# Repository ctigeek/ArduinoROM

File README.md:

# ArduinoROM

Open files using [KiCAD](https://kicad.org)

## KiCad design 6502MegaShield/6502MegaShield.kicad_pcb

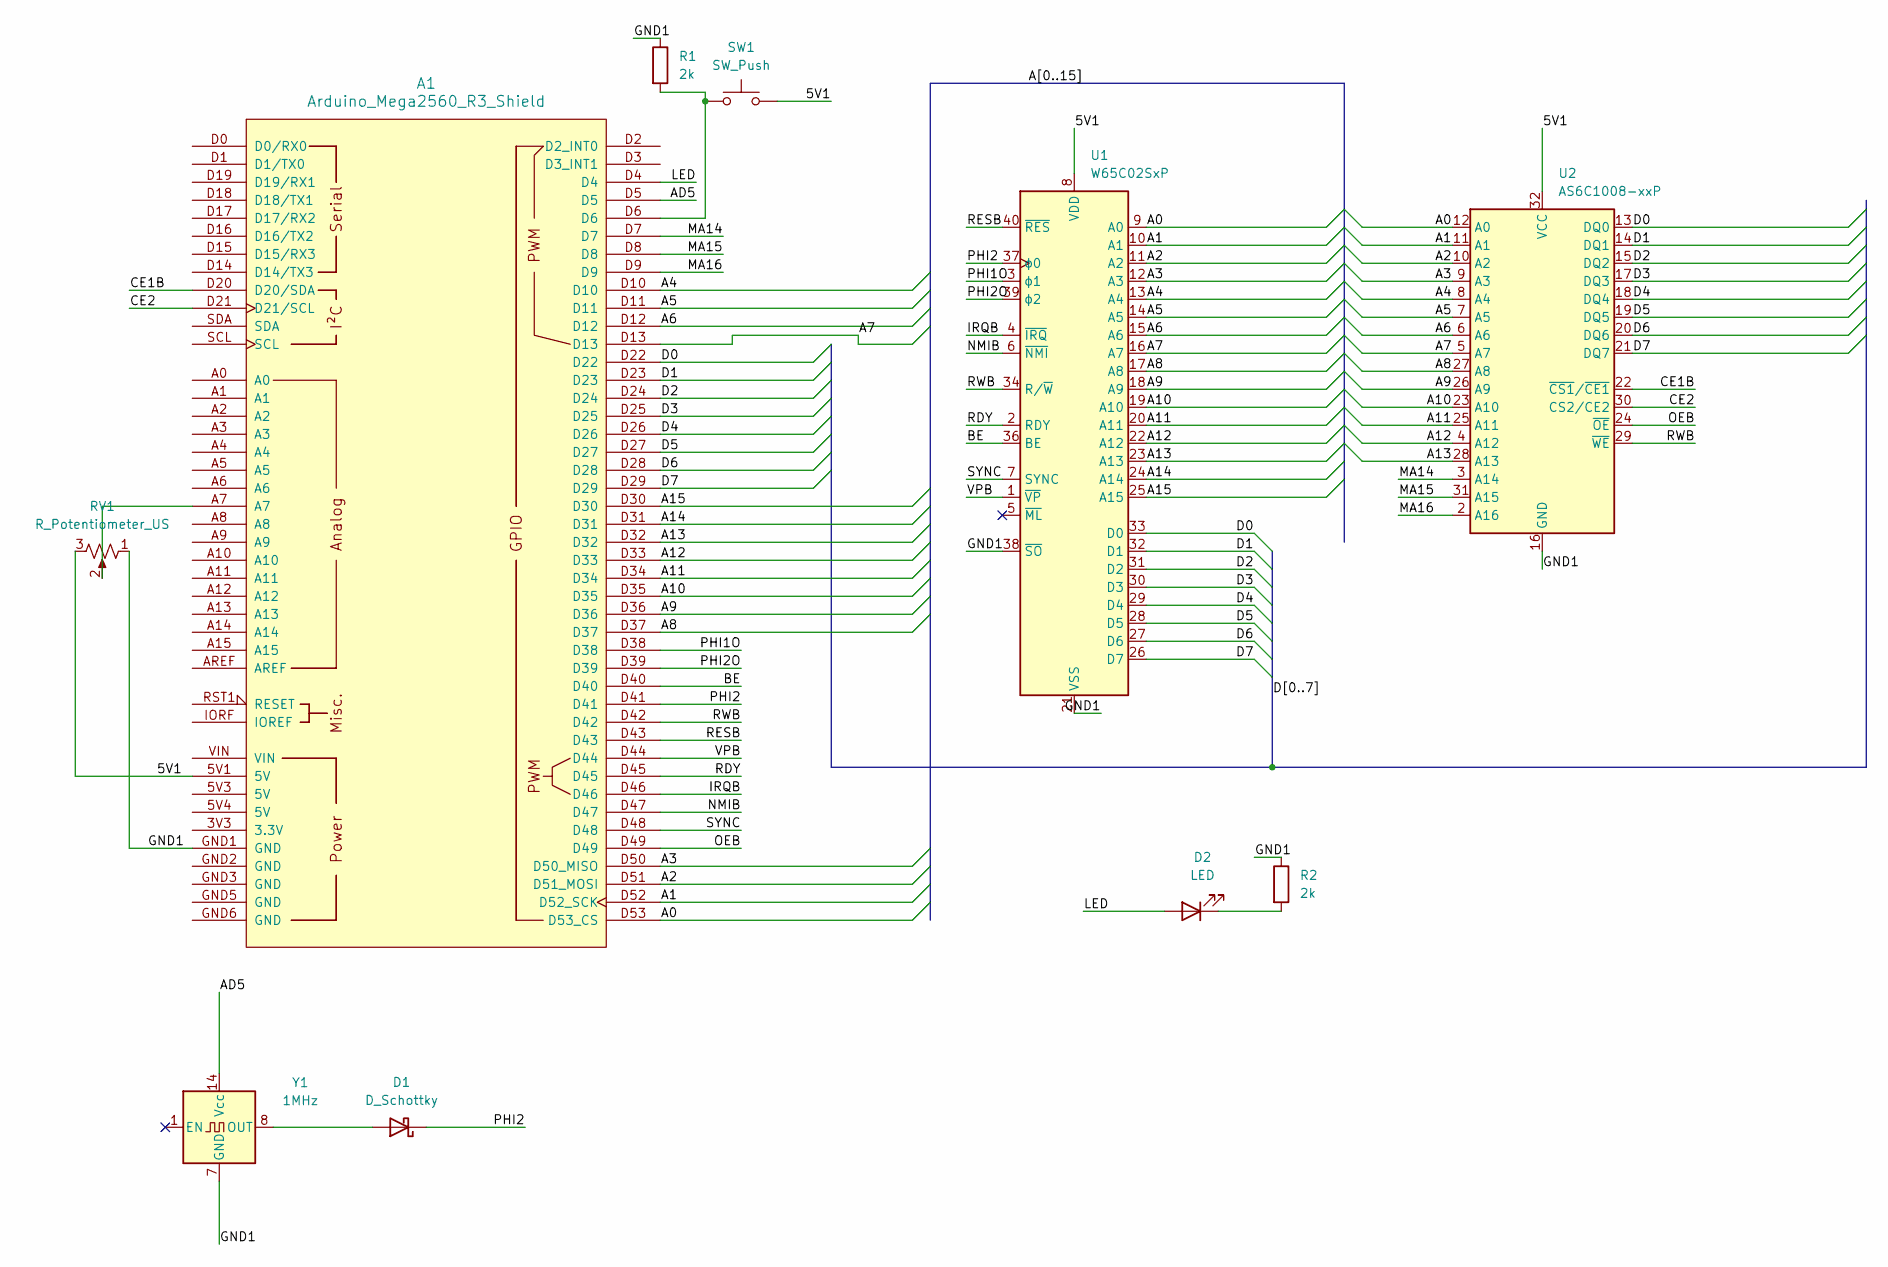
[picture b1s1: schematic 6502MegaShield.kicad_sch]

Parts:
A1: Arduino_Mega2560_R3_Shield
D1: D_Schottky; D_T-1_P5.08mm_Horizontal
D2: LED; LED_D3.0mm
R1, R2: 2k; R_Axial_DIN0204_L3.6mm_D1.6mm_P5.08mm_Horizontal
RV1: R_Potentiometer_US; Potentiometer_Bourns_3386P_Vertical
SW1: SW_Push; SW_PUSH_1P1T_6x3.5mm_H4.3_APEM_MJTP1243
U1: W65C02SxP; DIP-40_W15.24mm
U2: AS6C1008-xxP; DIP-32_W15.24mm
Y1: 1MHz; Oscillator_DIP-14

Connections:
/5V1: A1.5V1 (5V), RV1.3, SW1.2, U1.8 (VDD), U2.32 (VCC)
/A0: A1.D53 (D53_CS), U1.9 (A0), U2.12 (A0)
/A1: A1.D52 (D52_SCK), U1.10 (A1), U2.11 (A1)
/A2: A1.D51 (D51_MOSI), U1.11 (A2), U2.10 (A2)
/A3: A1.D50 (D50_MISO), U1.12 (A3), U2.9 (A3)
/A4: A1.D10, U1.13 (A4), U2.8 (A4)
/A5: A1.D11, U1.14 (A5), U2.7 (A5)
/A6: A1.D12, U1.15 (A6), U2.6 (A6)
/A7: A1.D13, U1.16 (A7), U2.5 (A7)
/A8: A1.D37, U1.17 (A8), U2.27 (A8)
/A9: A1.D36, U1.18 (A9), U2.26 (A9)
/A10: A1.D35, U1.19 (A10), U2.23 (A10)
/A11: A1.D34, U1.20 (A11), U2.25 (A11)
/A12: A1.D33, U1.22 (A12), U2.4 (A12)
/A13: A1.D32, U1.23 (A13), U2.28 (A13)
/A14: A1.D31, U1.24 (A14)
/A15: A1.D30, U1.25 (A15)
/AD5: A1.D5, Y1.14 (Vcc)
/BE: A1.D40, U1.36 (BE)
/CE1B: A1.D20 (D20/SDA), U2.22 (~CS1/~CE1)
/CE2: A1.D21 (D21/SCL), U2.30 (CS2/CE2)
/D0: A1.D22, U1.33 (D0), U2.13 (DQ0)
/D1: A1.D23, U1.32 (D1), U2.14 (DQ1)
/D2: A1.D24, U1.31 (D2), U2.15 (DQ2)
/D3: A1.D25, U1.30 (D3), U2.17 (DQ3)
/D4: A1.D26, U1.29 (D4), U2.18 (DQ4)
/D5: A1.D27, U1.28 (D5), U2.19 (DQ5)
/D6: A1.D28, U1.27 (D6), U2.20 (DQ6)
/D7: A1.D29, U1.26 (D7), U2.21 (DQ7)
/GND1: A1.GND1 (GND), R1.1, R2.1, RV1.1, U1.21 (VSS), U1.38 (~SO), U2.16 (GND), Y1.7 (GND)
/IRQB: A1.D46, U1.4 (~IRQ)
/LED: A1.D4, D2.2 (A)
/MA14: A1.D7, U2.3 (A14)
/MA15: A1.D8, U2.31 (A15)
/MA16: A1.D9, U2.2 (A16)
/NMIB: A1.D47, U1.6 (~NMI)
/OEB: A1.D49, U2.24 (~OE)
/PHI1O: A1.D38, U1.3 (ϕ1)
/PHI2: A1.D41, D1.1 (K), U1.37 (ϕ0)
/PHI2O: A1.D39, U1.39 (ϕ2)
/RDY: A1.D45, U1.2 (RDY)
/RESB: A1.D43, U1.40 (~RES)
/RWB: A1.D42, U1.34 (R/~W), U2.29 (~WE)
/SYNC: A1.D48, U1.7 (SYNC)
/VPB: A1.D44, U1.1 (~VP)
unnamed: A1.A7, RV1.2
unnamed: A1.D6, R1.2, SW1.1
unnamed: D1.2 (A), Y1.8 (OUT)
unnamed: D2.1 (K), R2.2

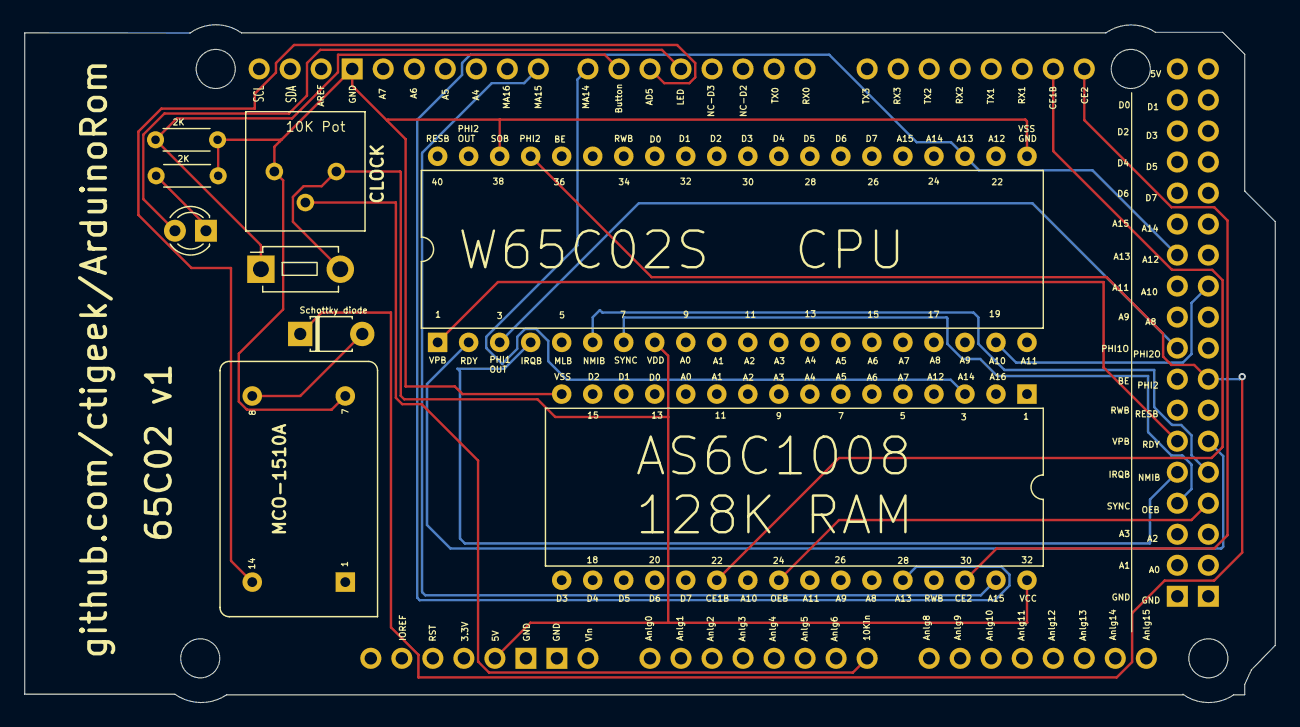
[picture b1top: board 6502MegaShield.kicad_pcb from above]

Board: 4 copper layers, 102.4 x 55.5 mm, 10 parts (0 on the bottom side), 49 nets.

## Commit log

2025-03-02 V1
    V1 of PCB for 65C02
